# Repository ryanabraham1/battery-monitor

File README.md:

# FRC Battery IR Monitor Node — hardware rev B (120 A pulse)

An inline node that sits between a charger and a 12 V FRC battery (charger → node → battery).
It measures internal resistance with a ~110 A / 100 ms pulse
load, and reports to a pit hub over wired CAN. No Wi-Fi or Bluetooth is used.

**Status:** schematic and layout are complete (ERC and DRC clean) and ready to order. Node
firmware, the Raspberry Pi hub software and printable cases are included. Nothing has been built
or tested on real hardware yet: the firmware compiles and the hub passes a simulated-node test.

- **[docs/BOM.md](docs/BOM.md): everything to buy, with purchase links.**
- **[docs/setup.md](docs/setup.md): full shopping list (including the Pi and CAN HAT), assembly,
  flashing, hub install, CAN wiring.** Start here.
- [docs/rev_b_120A.md](docs/rev_b_120A.md): what rev B changes from rev A (the `main` branch), its
  calculations, and what to check before the first pulse.
- [docs/design.md](docs/design.md): rev A calculations, parts that differ from the original brief, open questions.

## Board at a glance

- 100 × 80 mm, 2 layers, 2 oz copper, four #10 mounting holes (0.196 in)
- ESP32-S3 (radio unused), INA226 current/voltage monitor with a 0.5 mΩ Kelvin-sensed shunt
- Charger relay on its normally-closed contact, so an unpowered node leaves the charger connected, with its own 10 A fuse
- Pulse-load MOSFET with a hardware one-shot that cuts the load after ~220 ms even if firmware hangs
- Two RJ45 jacks for daisy-chained CAN, USB-C for flashing and serial, JST-XH socket for an optional PN532 NFC reader
- Bolt-down lug pads for BATT±, CHG±, LOAD± (off-board 0.1 Ω load bank) and two M5 studs that carry a 60 A MIDI fuse

| Top copper | Bottom copper |
|---|---|
|  |  |

| Component placement | Underside (3D) |
|---|---|
|  |  |

Full schematic: [hw/ir_node_schematic.pdf](hw/ir_node_schematic.pdf).

## Repository layout

| Folder | Contents |
|---|---|
| `docs/design.md` | Phase 1 design document: deviations, part choices, calculations, accuracy budget, open questions |
| `hw/` | KiCad 9 project: `ir_node.kicad_pro`, `.kicad_sch`, `.kicad_pcb`, schematic PDF, ERC and DRC reports |
| `fab/` | `ir_node_gerbers.zip` (Gerbers + drill), `pcbway/` (PCBWay BOM and placement file), `ir_node_BOM_full.csv`, JLCPCB BOM and CPL |
| `renders/` | PNG previews of each copper layer and 3D views |
| `firmware/` | ESP32-S3 node firmware (PlatformIO, Arduino framework) |
| `hub/` | Raspberry Pi hub: CAN logger, SQLite history, web page, installer, simulated node and test |
| `case/` | Printable STLs: node base and lid, Pi tray, optional NFC reader holder |
| `tools/` | The Python scripts that generate everything (run with KiCad's bundled Python) |

## Ordering (PCBWay)

1. PCB: upload `fab/ir_node_gerbers.zip`. Options: 2 layers, 100 × 80 mm, 1.6 mm FR-4,
   **2 oz finished copper**, HASL lead-free or ENIG. Minimum track/space on the board is 0.25/0.20 mm
   and the smallest via is 0.3 mm drill in a 0.7 mm pad.
2. Assembly: turnkey, top side only, 67 SMD placements of 42 part types. Upload
   `fab/pcbway/ir_node_BOM_PCBWay.csv` and `fab/pcbway/ir_node_CPL_PCBWay.csv`.
   To have PCBWay also fit the through-hole parts (relay, MOSFET, RJ45 ×2, JST-XH ×2, headers),
   upload `ir_node_BOM_PCBWay_with_THT.csv` instead and say so in the order notes.
3. The BOM lists a manufacturer part number for every line, the LCSC number as a sourcing
   reference, and which lines may be substituted. PCBWay emails about anything it wants to swap:
   passives, diodes and LEDs are free to swap like for like; the ICs, shunt R1, inductor L1, USB-C
   socket and buttons are not.
4. The placement file uses KiCad's own rotations and coordinates (no fab-specific offsets). Pin 1
   and polarity are marked on the silkscreen; `fab/layers_pdf/ir_node-F_Fab.pdf` is the assembly drawing.
5. If you did not order through-hole assembly, hand-solder the "THT" rows of
   `ir_node_BOM_PCBWay_with_THT.csv`.

The JLCPCB files (`ir_node_BOM_JLC.csv`, `ir_node_CPL_JLC.csv`, which carry JLC's rotation offsets)
are still generated for reference.

## What else you need

The PCB is one part of the system. The complete list with quantities, notes and rough prices is
in [docs/setup.md](docs/setup.md#1-everything-to-buy). In short:

- **Per node:** two 0.2 Ω 100 W resistors, normally-closed thermostat, 60 A MIDI fuse, two SB50 connectors, 6, 8 and 10 AWG wire, ring terminals, M4 and M5 hardware,
  an Ethernet patch cable, four #10-32 × 5/8 in screws, printed case
- **Hub (one per pit):** Raspberry Pi (3B+, 4 or 5), MCP2515 CAN HAT, microSD card, Pi power
  supply, one patch cable cut in half, printed tray

## Cases

## Regenerating

```
python tools/gen_sch.py     # schematic from tools/design.py
python tools/route.py <freerouting.jar>   # place, autoroute, pour
python tools/gen_fab.py     # BOM, CPL, Gerbers, renders
python tools/gen_case.py    # case STLs (needs: pip install manifold3d numpy pillow matplotlib)
python hub/test_hub.py      # hub against a simulated node (needs: pip install python-can)
```

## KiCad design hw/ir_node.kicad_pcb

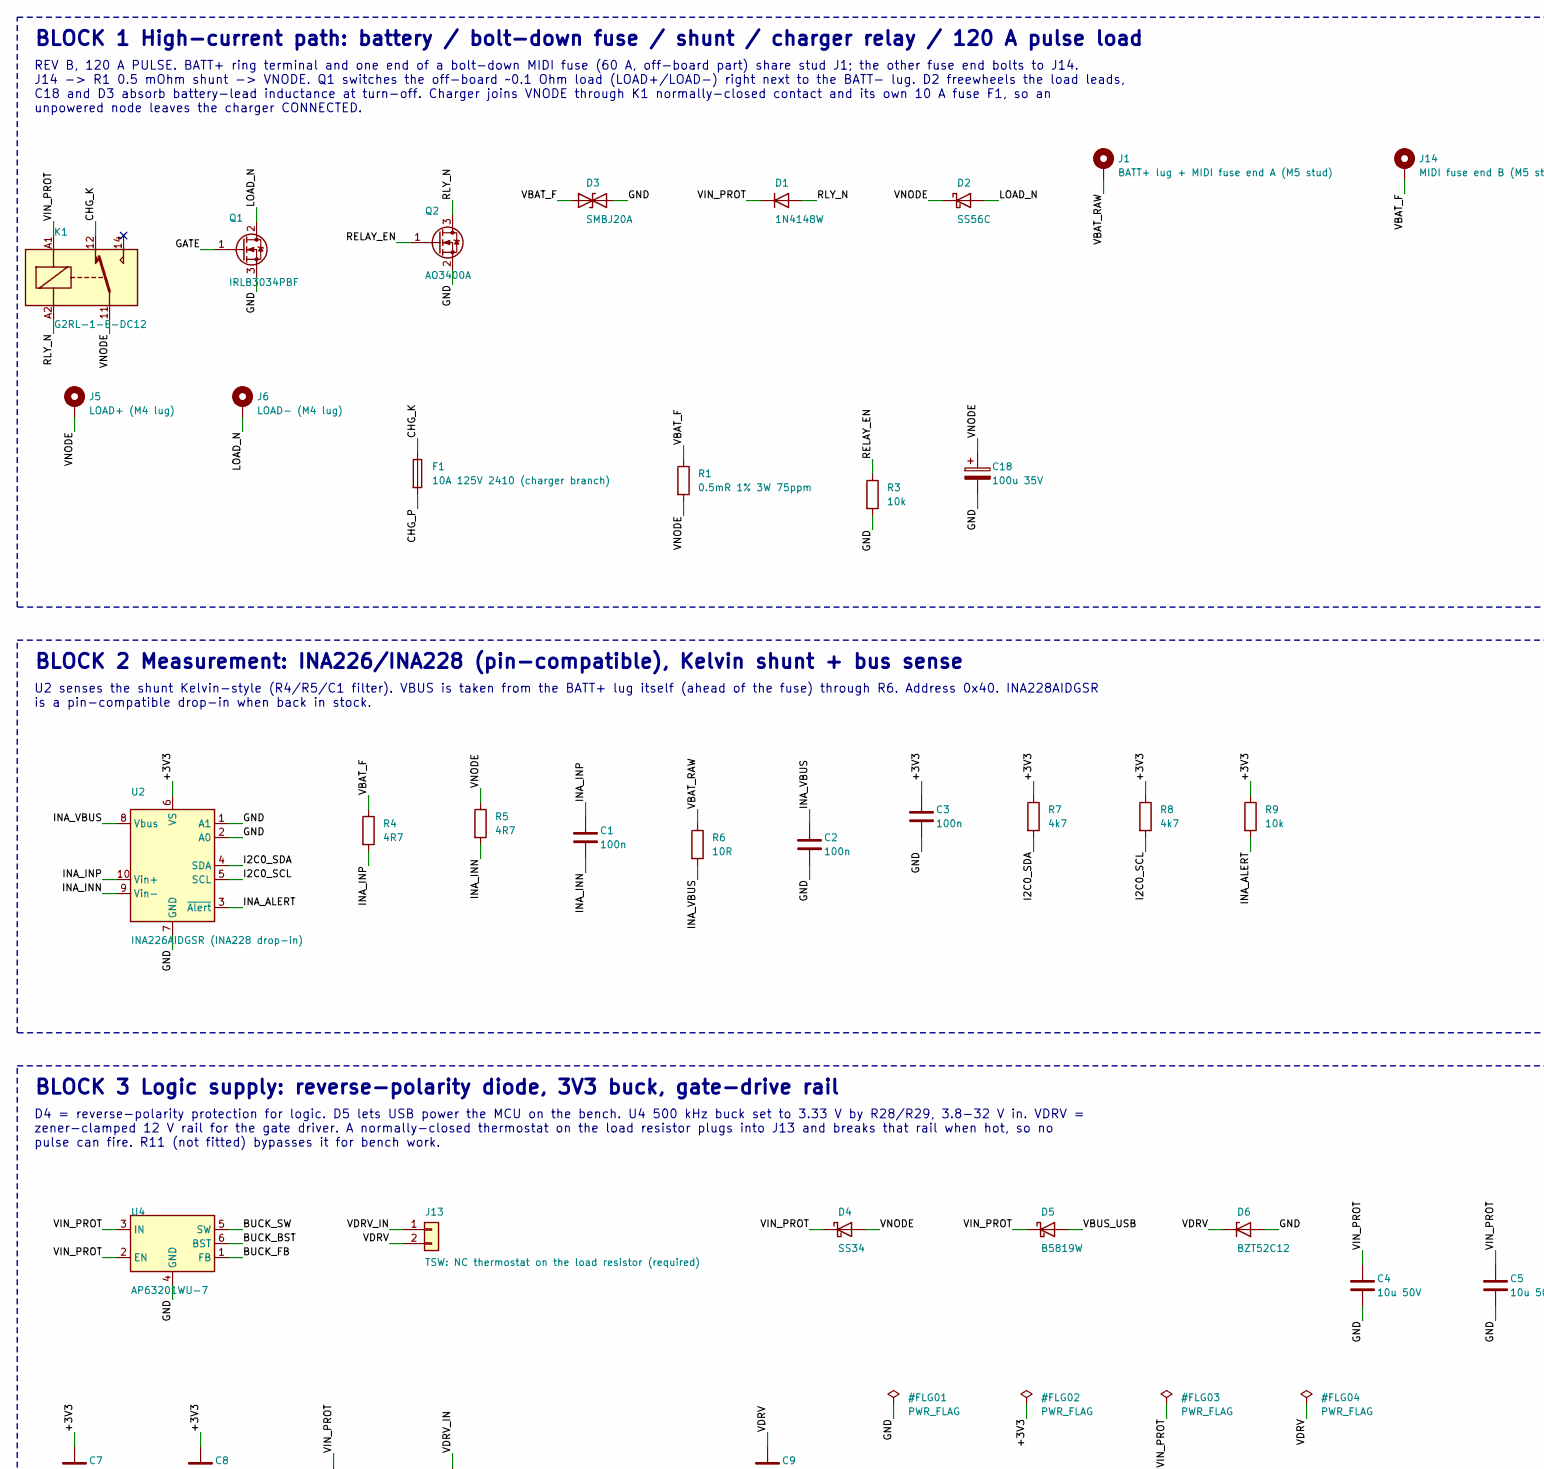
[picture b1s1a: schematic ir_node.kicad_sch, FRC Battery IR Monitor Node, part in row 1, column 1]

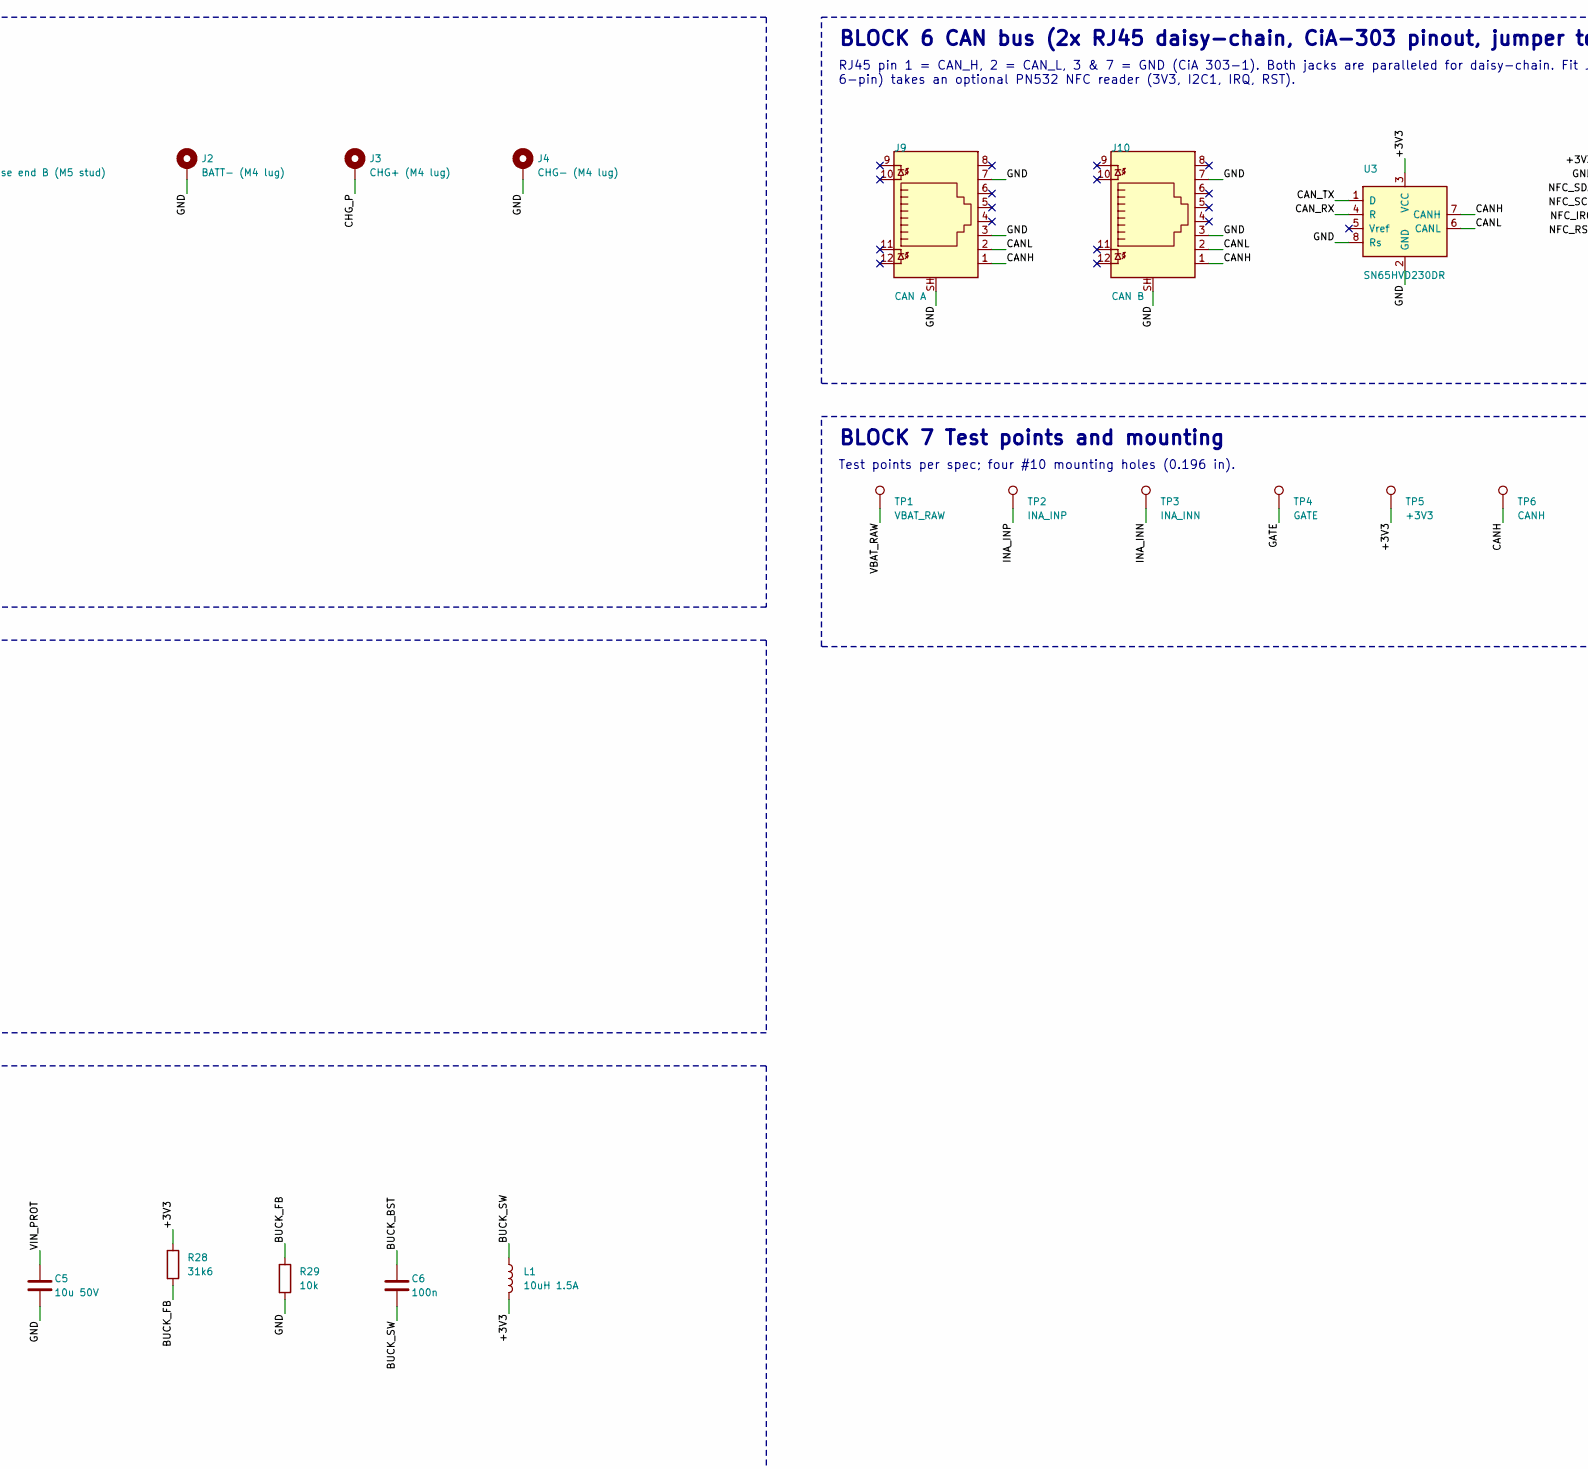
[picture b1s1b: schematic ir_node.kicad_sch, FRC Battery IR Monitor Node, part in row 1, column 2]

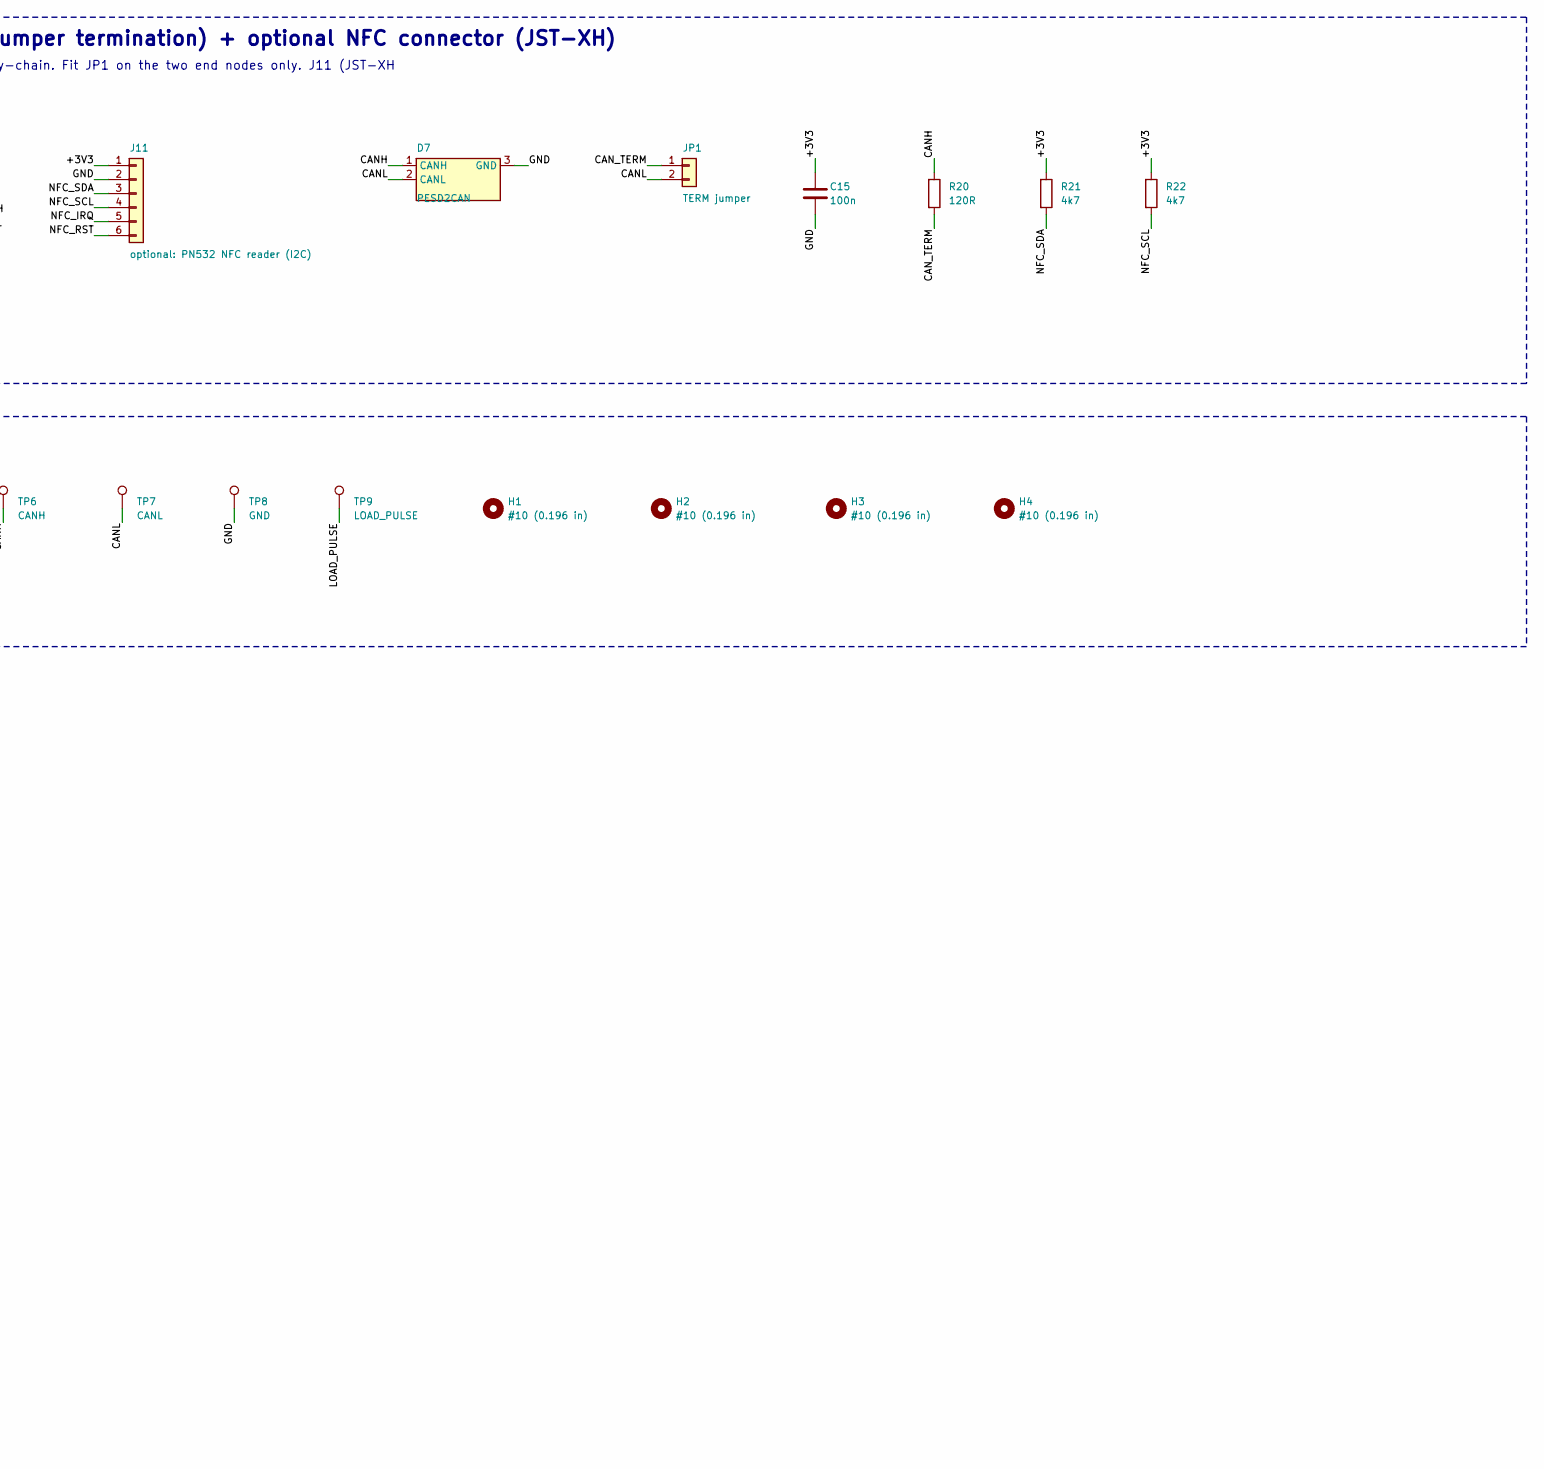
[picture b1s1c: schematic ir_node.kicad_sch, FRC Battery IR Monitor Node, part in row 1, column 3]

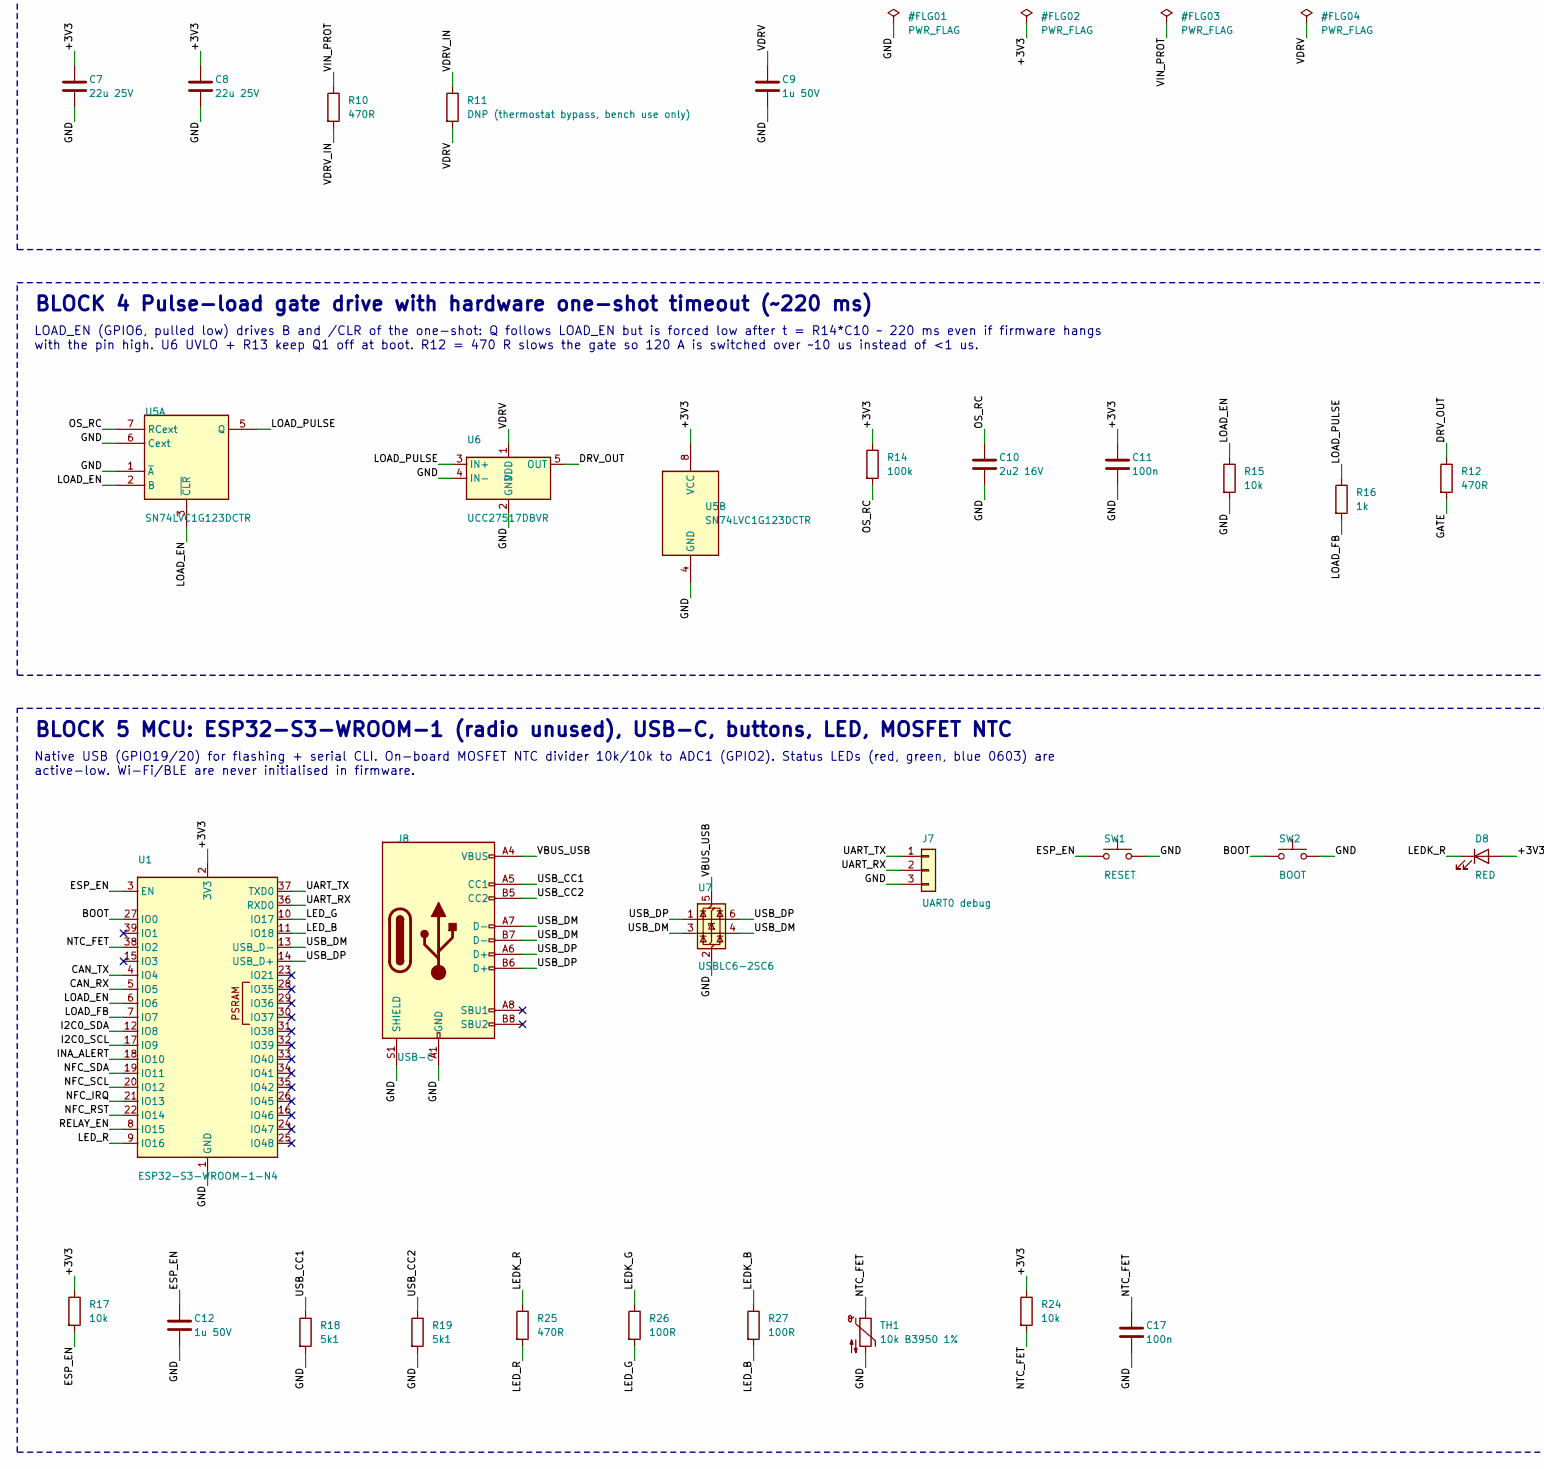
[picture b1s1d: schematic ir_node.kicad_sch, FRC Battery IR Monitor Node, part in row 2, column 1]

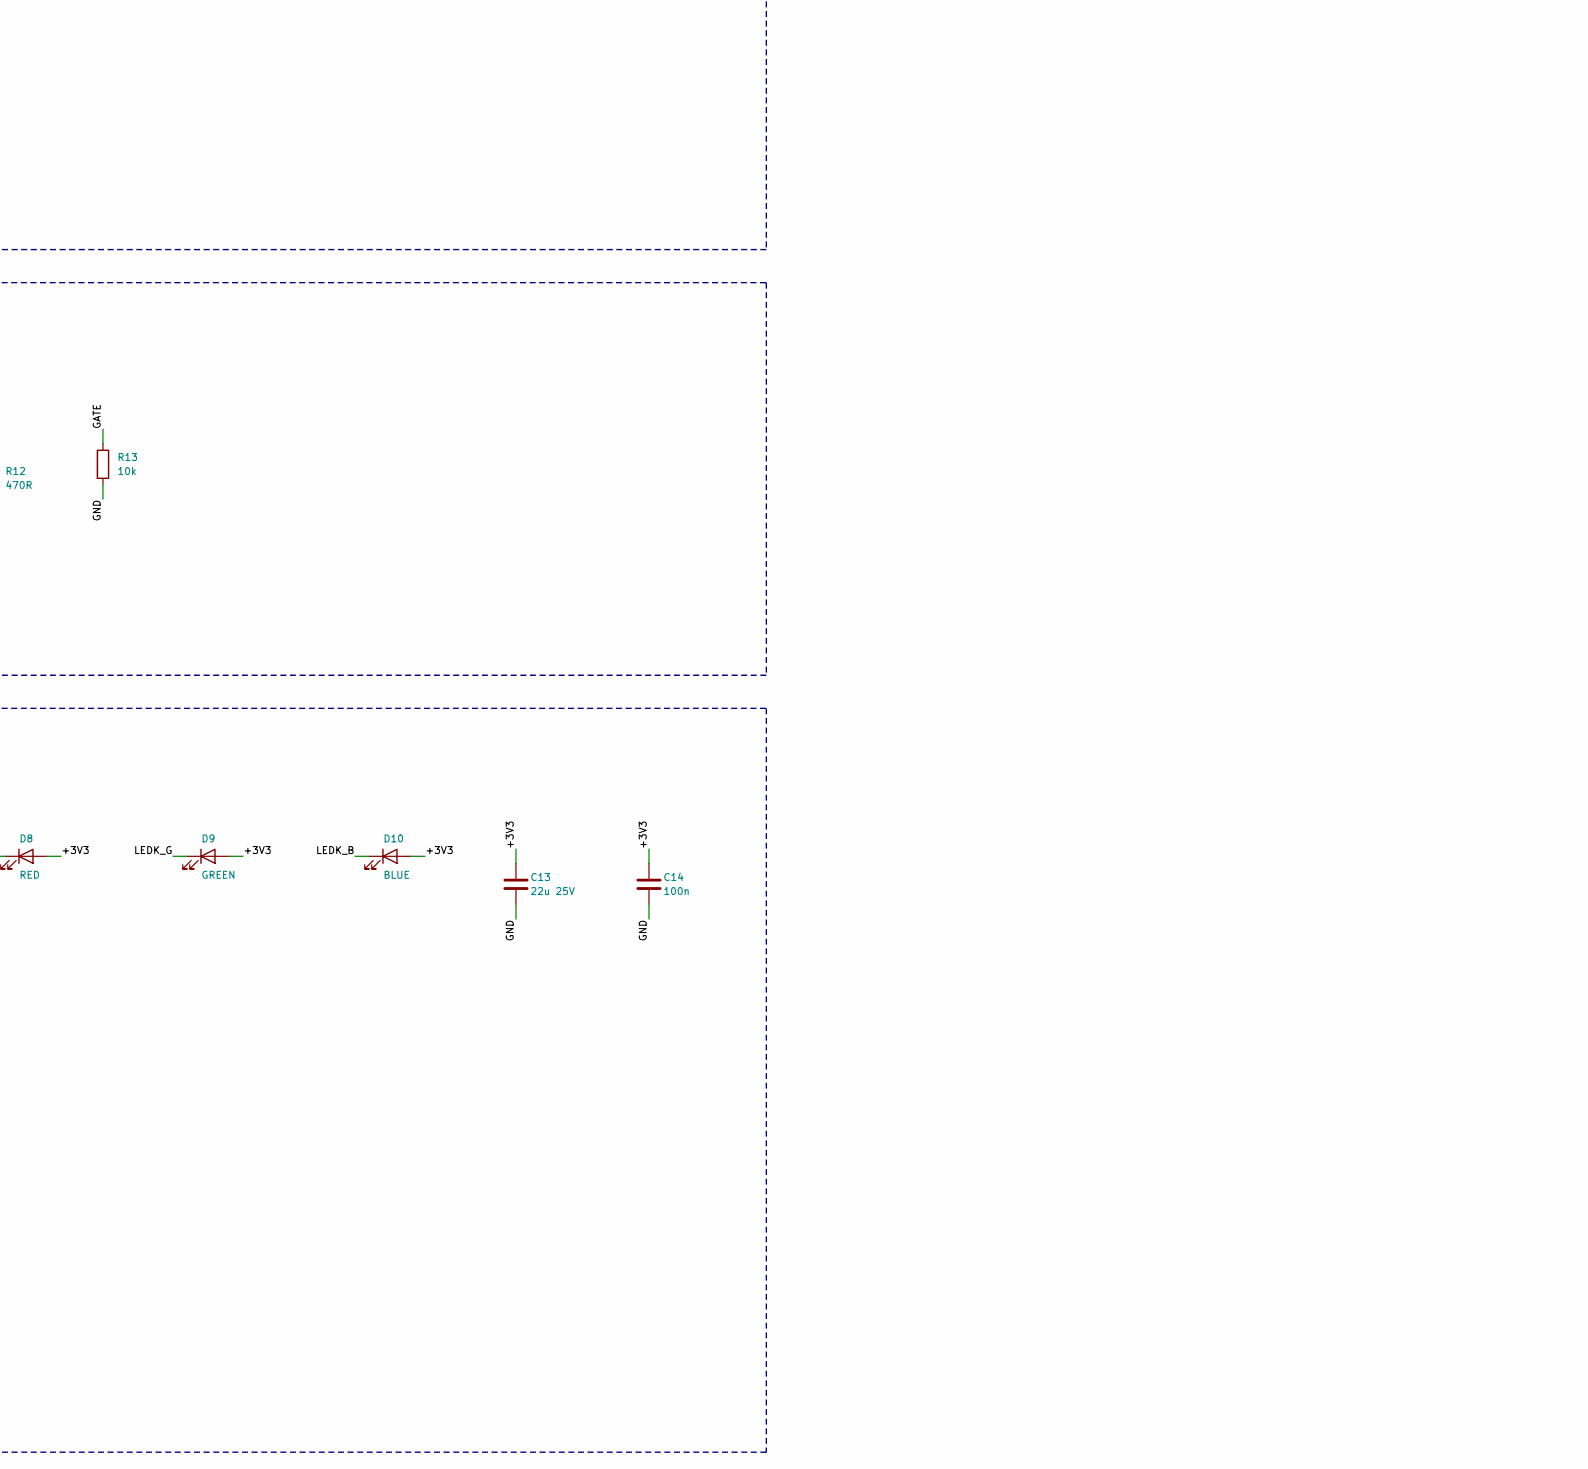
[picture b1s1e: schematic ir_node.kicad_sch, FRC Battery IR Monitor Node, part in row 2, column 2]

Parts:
C1, C2, C3, C6, C11, C14, C15, C17: 100n; C_0603_1608Metric; LCSC C14663
C4, C5: 10u 50V; C_1206_3216Metric; LCSC C13585
C7, C8, C13: 22u 25V; C_0805_2012Metric; LCSC C45783
C9, C12: 1u 50V; C_0603_1608Metric; LCSC C15849
C10: 2u2 16V; C_0603_1608Metric; LCSC C23630
C18: 100u 35V; CP_Elec_6.3x7.7; MPN KNSCHA RVT100UF35V67RV0034; LCSC C2836442
D1: 1N4148W; D_SOD-123; MPN 1N4148W; LCSC C81598
D2: SS56C; D_SMC; MPN MDD SS56C; LCSC C24138
D3: SMBJ20A; D_SMB; MPN BORN SMBJ20A; LCSC C151922
D4: SS34; D_SMA; MPN MDD SS34; LCSC C8678
D5: B5819W; D_SOD-123; MPN B5819W; LCSC C8598
D6: BZT52C12; D_SOD-123; MPN BZT52C12; LCSC C43491
D7: PESD2CAN; SOT-23; MPN UMW PESD2CAN; LCSC C2687131
D8: RED; LED_0603_1608Metric; MPN KENTO KT-0603R; LCSC C2286
D9: GREEN; LED_0603_1608Metric; MPN KENTO KT-0603G; LCSC C12624
D10: BLUE; LED_0603_1608Metric; MPN KENTO KT-0603B; LCSC C2288
F1: 10A 125V 2410 (charger branch); Fuse_Littelfuse-NANO2-451_453; MPN JDT JFC2410-2100TS; LCSC C136391
H1, H2, H3, H4: #10 (0.196 in); MountingHole_4.98mm_No10
J1: BATT+ lug + MIDI fuse end A (M5 stud); MountingHole_5.3mm_M5_Pad_Via
J2: BATT- (M4 lug); MountingHole_4.3mm_M4_Pad_Via
J3: CHG+ (M4 lug); MountingHole_4.3mm_M4_Pad_Via
J4: CHG- (M4 lug); MountingHole_4.3mm_M4_Pad_Via
J5: LOAD+ (M4 lug); MountingHole_4.3mm_M4_Pad_Via
J6: LOAD- (M4 lug); MountingHole_4.3mm_M4_Pad_Via
J7: UART0 debug; PinHeader_1x03_P2.54mm_Vertical; MPN 2.54mm header 1x3
J8: USB-C; USB_C_Receptacle_HRO_TYPE-C-31-M-12; MPN HRO TYPE-C-31-M-12; LCSC C165948
J9: CAN A; RJ45_Connfly_DS1128-09-S8xx-S_Horizontal; MPN Connfly DS1128-09-S8B8X; LCSC C86578
J10: CAN B; RJ45_Connfly_DS1128-09-S8xx-S_Horizontal; MPN Connfly DS1128-09-S8B8X; LCSC C86578
J11: optional: PN532 NFC reader (I2C); JST_XH_B6B-XH-A_1x06_P2.50mm_Vertical; MPN XH-6A (optional); LCSC C5663
J13: TSW: NC thermostat on the load resistor (required); JST_XH_B2B-XH-A_1x02_P2.50mm_Vertical; MPN XH-2A; LCSC C20079
J14: MIDI fuse end B (M5 stud); MountingHole_5.3mm_M5_Pad_Via
JP1: TERM jumper; PinHeader_1x02_P2.54mm_Vertical; MPN 2.54mm header 1x2 + jumper cap
K1: G2RL-1-E-DC12; Relay_SPDT_Omron_G2RL-1-E; MPN Omron G2RL-1-E-DC12; LCSC C58243
L1: 10uH 1.5A; L_Sunlord_SWPA4030S; MPN Sunlord SWPA4030S100MT; LCSC C38117
Q1: IRLB3034PBF; TO-220-3_Vertical; MPN Infineon IRLB3034PBF; LCSC C144151
Q2: AO3400A; SOT-23; MPN AOS AO3400A; LCSC C20917
R1: 0.5mR 1% 3W 75ppm; R_2512_6332Metric; MPN TA-I RLM25FEGMR50M; LCSC C710260
R3, R9, R13, R15, R17, R24, R29: 10k; R_0603_1608Metric; LCSC C25804
R4, R5: 4R7; R_0603_1608Metric; LCSC C23164
R6: 10R; R_0603_1608Metric; LCSC C22859
R7, R8, R21, R22: 4k7; R_0603_1608Metric; LCSC C23162
R10, R12, R25: 470R; R_0603_1608Metric; LCSC C23179
R11: DNP (thermostat bypass, bench use only); R_0603_1608Metric
R14: 100k; R_0603_1608Metric; LCSC C25803
R16: 1k; R_0603_1608Metric; LCSC C21190
R18, R19: 5k1; R_0603_1608Metric; LCSC C23186
R20: 120R; R_0603_1608Metric; LCSC C22787
R26, R27: 100R; R_0603_1608Metric; LCSC C22775
R28: 31k6; R_0603_1608Metric; LCSC C25967
SW1: RESET; SW_Push_1P1T_XKB_TS-1187A; MPN XKB TS-1187A-B-A-B; LCSC C318884
SW2: BOOT; SW_Push_1P1T_XKB_TS-1187A; MPN XKB TS-1187A-B-A-B; LCSC C318884
TH1: 10k B3950 1%; R_0603_1608Metric; MPN KUU KNTC0603/10KF3950; LCSC C2892547
TP1: VBAT_RAW; TestPoint_THTPad_D2.0mm_Drill1.0mm
TP2: INA_INP; TestPoint_THTPad_D2.0mm_Drill1.0mm
TP3: INA_INN; TestPoint_THTPad_D2.0mm_Drill1.0mm
TP4: GATE; TestPoint_THTPad_D2.0mm_Drill1.0mm
TP5: +3V3; TestPoint_THTPad_D2.0mm_Drill1.0mm
TP6: CANH; TestPoint_THTPad_D2.0mm_Drill1.0mm
TP7: CANL; TestPoint_THTPad_D2.0mm_Drill1.0mm
TP8: GND; TestPoint_THTPad_D2.0mm_Drill1.0mm
TP9: LOAD_PULSE; TestPoint_THTPad_D2.0mm_Drill1.0mm
U1: ESP32-S3-WROOM-1-N4; ESP32-S3-WROOM-1; MPN Espressif ESP32-S3-WROOM-1-N4; LCSC C2913197
U2: INA226AIDGSR (INA228 drop-in); VSSOP-10_3x3mm_P0.5mm; MPN TI INA226AIDGSR; LCSC C49851
U3: SN65HVD230DR; SOIC-8_3.9x4.9mm_P1.27mm; MPN TI SN65HVD230DR; LCSC C12084
U4: AP63201WU-7; TSOT-23-6; MPN Diodes AP63201WU-7; LCSC C2071044
U5: SN74LVC1G123DCTR; SSOP-8_2.95x2.8mm_P0.65mm; MPN TI SN74LVC1G123DCTR; LCSC C123302
U6: UCC27517DBVR; SOT-23-5; MPN TI UCC27517DBVR; LCSC C99395
U7: USBLC6-2SC6; SOT-23-6; MPN ST USBLC6-2SC6; LCSC C7519

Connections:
/+3V3: C3.1, C7.1, C8.1, C11.1, C13.1, C14.1, C15.1, D8.2 (A), D9.2 (A), D10.2 (A), J11.1, L1.2, R7.1, R8.1, R9.1, R14.1, R17.1, R21.1, R22.1, R24.1, R28.1, TP5.1, U1.2 (3V3), U2.6 (VS), U3.3 (VCC), U5.8 (VCC)
/BOOT: SW2.1, U1.27 (IO0)
/BUCK_BST: C6.1, U4.6 (BST)
/BUCK_FB: R28.2, R29.1, U4.1 (FB)
/BUCK_SW: C6.2, L1.1, U4.5 (SW)
/CANH: D7.1 (CANH), J9.1, J10.1, R20.1, TP6.1, U3.7 (CANH)
/CANL: D7.2 (CANL), J9.2, J10.2, JP1.2, TP7.1, U3.6 (CANL)
/CAN_RX: U1.5 (IO5), U3.4 (R)
/CAN_TERM: JP1.1, R20.2
/CAN_TX: U1.4 (IO4), U3.1 (D)
/CHG_K: F1.1, K1.12
/CHG_P: F1.2, J3.1
/DRV_OUT: R12.1, U6.5 (OUT)
/ESP_EN: C12.1, R17.2, SW1.1, U1.3 (EN)
/GATE: Q1.1 (G), R12.2, R13.1, TP4.1
/GND: C2.2, C3.2, C4.2, C5.2, C7.2, C8.2, C9.2, C10.2, C11.2, C12.2, C13.2, C14.2, C15.2, C17.2, C18.2, D3.2 (A2), D6.2 (A), D7.3 (GND), J2.1, J4.1, J7.3, J8.A1 (GND), J8.A12 (GND), J8.B1 (GND), J8.B12 (GND), J8.S1 (SHIELD), J9.3, J9.7, J9.SH, J10.3, J10.7, J10.SH, J11.2, Q1.3 (S), Q2.2 (S), R3.2, R13.2, R15.2, R18.2, R19.2, R29.2, SW1.2, SW2.2, TH1.2, TP8.1, U1.1 (GND), U1.40 (GND), U1.41 (GND), U2.1 (A1), U2.2 (A0), U2.7 (GND), U3.2 (GND), U3.8 (Rs), U4.4 (GND), U5.1 (~A), U5.4 (GND), U5.6 (Cext), U6.2 (GND), U6.4 (IN-), U7.2 (GND)
/I2C0_SCL: R8.2, U1.17 (IO9), U2.5 (SCL)
/I2C0_SDA: R7.2, U1.12 (IO8), U2.4 (SDA)
/INA_ALERT: R9.2, U1.18 (IO10), U2.3 (~Alert)
/INA_INN: C1.2, R5.2, TP3.1, U2.9 (Vin-)
/INA_INP: C1.1, R4.2, TP2.1, U2.10 (Vin+)
/INA_VBUS: C2.1, R6.2, U2.8 (Vbus)
/LEDK_B: D10.1 (K), R27.1
/LEDK_G: D9.1 (K), R26.1
/LEDK_R: D8.1 (K), R25.1
/LED_B: R27.2, U1.11 (IO18)
/LED_G: R26.2, U1.10 (IO17)
/LED_R: R25.2, U1.9 (IO16)
/LOAD_EN: R15.1, U1.6 (IO6), U5.2 (B), U5.3 (~CLR)
/LOAD_FB: R16.2, U1.7 (IO7)
/LOAD_N: D2.2 (A), J6.1, Q1.2 (D)
/LOAD_PULSE: R16.1, TP9.1, U5.5 (Q), U6.3 (IN+)
/NFC_IRQ: J11.5, U1.21 (IO13)
/NFC_RST: J11.6, U1.22 (IO14)
/NFC_SCL: J11.4, R22.2, U1.20 (IO12)
/NFC_SDA: J11.3, R21.2, U1.19 (IO11)
/NTC_FET: C17.1, R24.2, TH1.1, U1.38 (IO2)
/OS_RC: C10.1, R14.2, U5.7 (RCext)
/RELAY_EN: Q2.1 (G), R3.1, U1.8 (IO15)
/RLY_N: D1.2 (A), K1.A2, Q2.3 (D)
/UART_RX: J7.2, U1.36 (RXD0)
/UART_TX: J7.1, U1.37 (TXD0)
/USB_CC1: J8.A5 (CC1), R18.1
/USB_CC2: J8.B5 (CC2), R19.1
/USB_DM: J8.A7 (D-), J8.B7 (D-), U1.13 (USB_D-), U7.3 (I/O2), U7.4 (I/O2)
/USB_DP: J8.A6 (D+), J8.B6 (D+), U1.14 (USB_D+), U7.1 (I/O1), U7.6 (I/O1)
/VBAT_F: D3.1 (A1), J14.1, R1.1, R4.1
/VBAT_RAW: J1.1, R6.1, TP1.1
/VBUS_USB: D5.2 (A), J8.A4 (VBUS), J8.A9 (VBUS), J8.B4 (VBUS), J8.B9 (VBUS), U7.5 (VBUS)
/VDRV: C9.1, D6.1 (K), J13.2, R11.2, U6.1 (VDD)
/VDRV_IN: J13.1, R10.2, R11.1
/VIN_PROT: C4.1, C5.1, D1.1 (K), D4.1 (K), D5.1 (K), K1.A1, R10.1, U4.2 (EN), U4.3 (IN)
/VNODE: C18.1, D2.1 (K), D4.2 (A), J5.1, K1.11, R1.2, R5.1

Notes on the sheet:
BLOCK 1 High-current path: battery / bolt-down fuse / shunt / charger relay / 120 A pulse load
REV B, 120 A PULSE. BATT+ ring terminal and one end of a bolt-down MIDI fuse (60 A, off-board part) share stud J1; the other fuse end bolts to J14. J14 -> R1 0.5 mOhm shunt -> VNODE. Q1 switches the off-board ~0.1 Ohm load (LOAD+/LOAD-) right next to the BATT- lug. D2 freewheels the load leads, C18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
BLOCK 2 Measurement: INA226/INA228 (pin-compatible), Kelvin shunt + bus sense
U2 senses the shunt Kelvin-style (R4/R5/C1 filter). VBUS is taken from the BATT+ lug itself (ahead of the fuse) through R6. Address 0x40. INA228AIDGSR is a pin-compatible drop-in when back in stock.
BLOCK 3 Logic supply: reverse-polarity diode, 3V3 buck, gate-drive rail
D4 = reverse-polarity protection for logic. D5 lets USB power the MCU on the bench. U4 500 kHz buck set to 3.33 V by R28/R29, 3.8-32 V in. VDRV = zener-clamped 12 V rail for the gate driver. A normally-closed thermostat on the load resistor plugs into J13 and breaks that rail when hot, so no pulse 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
BLOCK 4 Pulse-load gate drive with hardware one-shot timeout (~220 ms)
LOAD_EN (GPIO6, pulled low) drives B and /CLR of the one-shot: Q follows LOAD_EN but is forced low after t = R14*C10 ~ 220 ms even if firmware hangs with the pin high. U6 UVLO + R13 keep Q1 off at boot. R12 = 470 R slows the gate so 120 A is switched over ~10 us instead of <1 us.
BLOCK 5 MCU: ESP32-S3-WROOM-1 (radio unused), USB-C, buttons, LED, MOSFET NTC
Native USB (GPIO19/20) for flashing + serial CLI. On-board MOSFET NTC divider 10k/10k to ADC1 (GPIO2). Status LEDs (red, green, blue 0603) are active-low. Wi-Fi/BLE are never initialised in firmware.
BLOCK 6 CAN bus (2x RJ45 daisy-chain, CiA-303 pinout, jumper termination) + optional NFC connector (JST-XH)
RJ45 pin 1 = CAN_H, 2 = CAN_L, 3 & 7 = GND (CiA 303-1). Both jacks are paralleled for daisy-chain. Fit JP1 on the two end nodes only. J11 (JST-XH 6-pin) takes an optional PN532 NFC reader (3V3, I2C1, IRQ, RST).
BLOCK 7 Test points and mounting
Test points per spec; four #10 mounting holes (0.196 in).

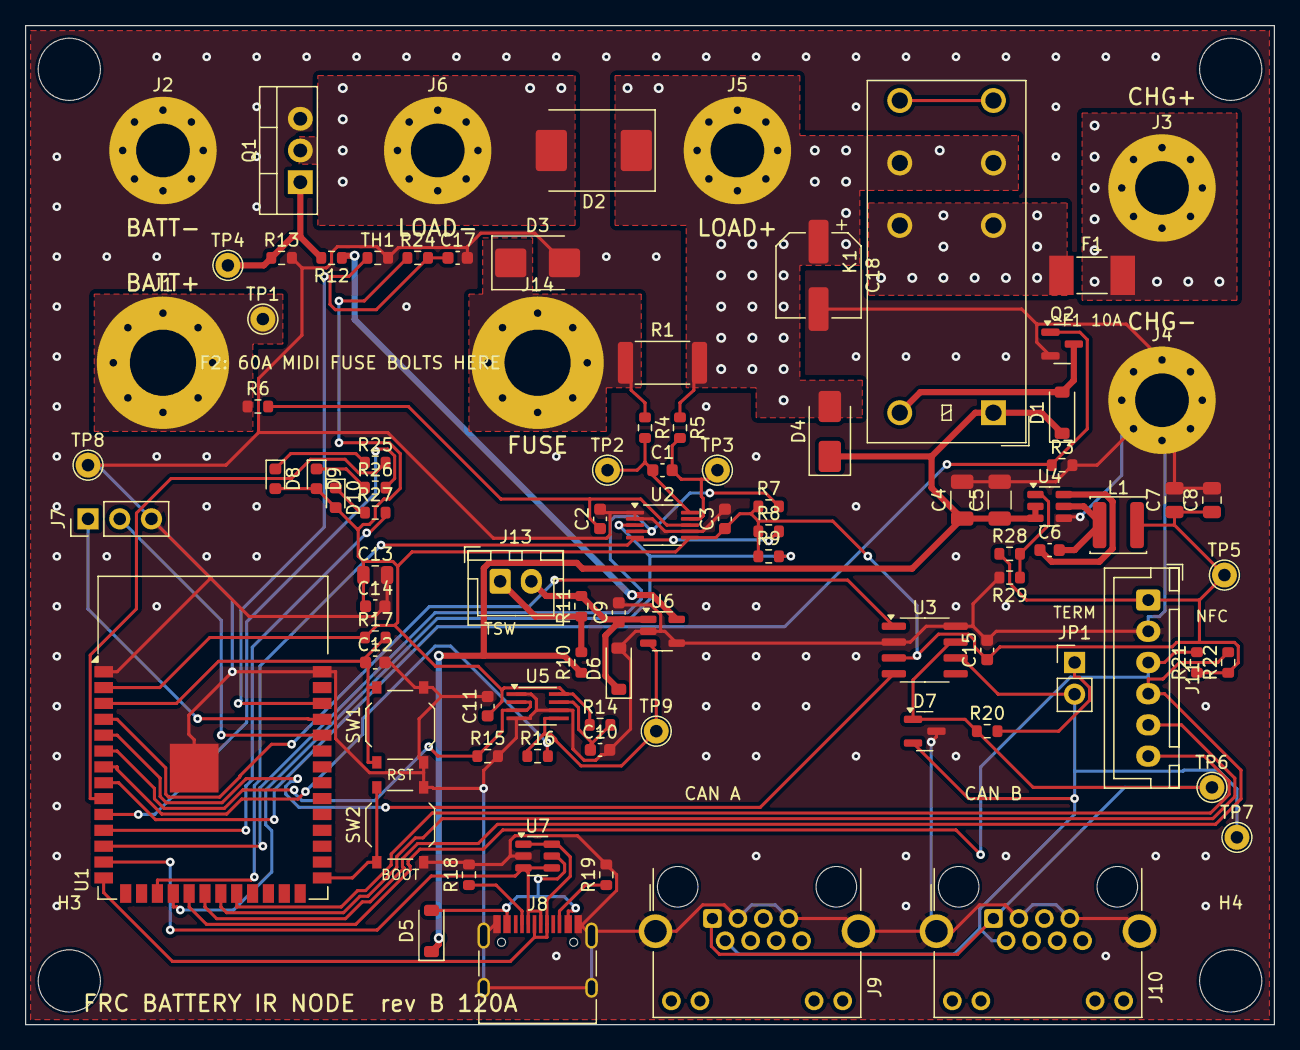
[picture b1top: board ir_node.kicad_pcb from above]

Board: 2 copper layers, 100.0 x 80.0 mm, 96 parts (0 on the bottom side), 53 nets.

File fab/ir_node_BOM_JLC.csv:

Comment,Designator,Footprint,LCSC Part #
100n,"C1,C2,C3,C6,C11,C14,C15,C17",C_0603_1608Metric,C14663
10u 50V,"C4,C5",C_1206_3216Metric,C13585
22u 25V,"C7,C8,C13",C_0805_2012Metric,C45783
1u 50V,"C9,C12",C_0603_1608Metric,C15849
2u2 16V,C10,C_0603_1608Metric,C23630
100u 35V,C18,CP_Elec_6.3x7.7,C2836442
1N4148W,D1,D_SOD-123,C81598
SS56C,D2,D_SMC,C24138
SMBJ20A,D3,D_SMB,C151922
SS34,D4,D_SMA,C8678
B5819W,D5,D_SOD-123,C8598
BZT52C12,D6,D_SOD-123,C43491
PESD2CAN,D7,SOT-23,C2687131
RED,D8,LED_0603_1608Metric,C2286
GREEN,D9,LED_0603_1608Metric,C12624
BLUE,D10,LED_0603_1608Metric,C2288
10A 125V 2410 (charger branch),F1,Fuse_Littelfuse-NANO2-451_453,C136391
USB-C,J8,USB_C_Receptacle_HRO_TYPE-C-31-M-12,C165948
10uH 1.5A,L1,L_Sunlord_SWPA4030S,C38117
AO3400A,Q2,SOT-23,C20917
0.5mR 1% 3W 75ppm,R1,R_2512_6332Metric,C710260
10k,"R3,R9,R13,R15,R17,R24,R29",R_0603_1608Metric,C25804
4R7,"R4,R5",R_0603_1608Metric,C23164
10R,R6,R_0603_1608Metric,C22859
4k7,"R7,R8,R21,R22",R_0603_1608Metric,C23162
470R,"R10,R12,R25",R_0603_1608Metric,C23179
100k,R14,R_0603_1608Metric,C25803
1k,R16,R_0603_1608Metric,C21190
5k1,"R18,R19",R_0603_1608Metric,C23186
120R,R20,R_0603_1608Metric,C22787
100R,"R26,R27",R_0603_1608Metric,C22775
31k6,R28,R_0603_1608Metric,C25967
RESET,SW1,SW_Push_1P1T_XKB_TS-1187A,C318884
BOOT,SW2,SW_Push_1P1T_XKB_TS-1187A,C318884
10k B3950 1%,TH1,R_0603_1608Metric,C2892547
ESP32-S3-WROOM-1-N4,U1,ESP32-S3-WROOM-1,C2913197
INA226AIDGSR (INA228 drop-in),U2,VSSOP-10_3x3mm_P0.5mm,C49851
SN65HVD230DR,U3,SOIC-8_3.9x4.9mm_P1.27mm,C12084
AP63201WU-7,U4,TSOT-23-6,C2071044
SN74LVC1G123DCTR,U5,SSOP-8_2.95x2.8mm_P0.65mm,C123302
UCC27517DBVR,U6,SOT-23-5,C99395
USBLC6-2SC6,U7,SOT-23-6,C7519

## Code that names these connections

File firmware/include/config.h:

// Pin map and fixed constants for the IR node, hardware rev B (120 A pulse load).
// Must match tools/design.py (the schematic source).
#pragma once
#include <Arduino.h>

// ---- GPIO ----
#define PIN_CAN_TX     4
#define PIN_CAN_RX     5
#define PIN_LOAD_EN    6   // high = request pulse (one-shot caps it at ~220 ms in hardware)
#define PIN_LOAD_FB    7   // one-shot output readback, high while the gate driver is enabled
#define PIN_RELAY_EN   15  // high = relay energised = charger DISCONNECTED (NC contact opens)
#define PIN_LED_R      16  // three separate 0603 LEDs, active low
#define PIN_LED_G      17
#define PIN_LED_B      18
#define PIN_I2C0_SDA   8   // INA226
#define PIN_I2C0_SCL   9
#define PIN_INA_ALERT  10
#define PIN_NFC_SDA    11  // PN532 on its own bus
#define PIN_NFC_SCL    12
#define PIN_NFC_IRQ    13
#define PIN_NFC_RST    14
#define PIN_NTC_FET    2   // ADC1_CH1, on-board NTC next to the MOSFET

// ---- measurement ----
#define INA_ADDR         0x40
#define SHUNT_OHMS       0.0005f // INA226 full scale = 163 A
#define PULSE_MS         100     // firmware pulse length
#define PULSE_SKIP_MS    40      // ignore samples before this (lead inductance, driver rise, averaging window)
#define BASELINE_SAMPLES 16
#define MIN_TEST_GAP_MS  30000   // duty limit for the load resistors and the 60 A fuse
#define MIN_TEST_VOLTS   10.5f
#define MAX_FET_TEMP_C   80
#define DI_MIN_A         60.0f   // below this the load bank / thermostat is open or a lug is loose
#define DI_MAX_A         155.0f
#define STUCK_A          3.0f    // load current still flowing 60 ms after the pulse = stuck MOSFET
#define BATT_PRESENT_V   9.0f

// ---- CAN (250 kbit/s, 11-bit IDs, little-endian payloads) ----
#define CAN_ID_CMD     0x080   // + node id, or exactly 0x080 for "all nodes"
#define CAN_ID_STATUS  0x100   // + node id, 1 Hz
#define CAN_ID_UID     0x180   // + node id, on change and every 5 s
#define CAN_ID_RESULT  0x200   // + node id, sent 3x after each test

enum Cmd : uint8_t { CMD_TEST = 1, CMD_CHARGER = 2, CMD_IDENTIFY = 3, CMD_CLEAR_FAULT = 4 };

enum State : uint8_t {
  ST_NO_BATT = 0,
  ST_IDLE = 1,       // battery present, not charging
  ST_CHARGING = 2,
  ST_SETTLE = 3,     // charger disconnected, waiting before the pulse
  ST_TEST = 4,
  ST_FAULT_STUCK = 0x80,  // load current did not stop after the pulse (latched)
};

enum Err : uint8_t {
  ERR_NONE = 0,
  ERR_LOW_VOLTAGE = 1,
  ERR_HOT = 2,
  ERR_NO_PULSE = 3,    // one-shot / driver never turned on
  ERR_LOAD_OPEN = 4,   // pulse current too low: resistor missing, thermostat open, bad lug
  ERR_OVERCURRENT = 5,
  ERR_INA = 6,         // no samples from the INA226
  ERR_STUCK = 7,
};

// status flags
#define FLAG_TAG        0x01
#define FLAG_CHG_CONN   0x02
#define FLAG_NFC_OK     0x04
#define FLAG_INA_OK     0x08
#define FLAG_RESULT_OK  0x10
